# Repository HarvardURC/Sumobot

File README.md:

# Sumobot
Repository for Sumobot

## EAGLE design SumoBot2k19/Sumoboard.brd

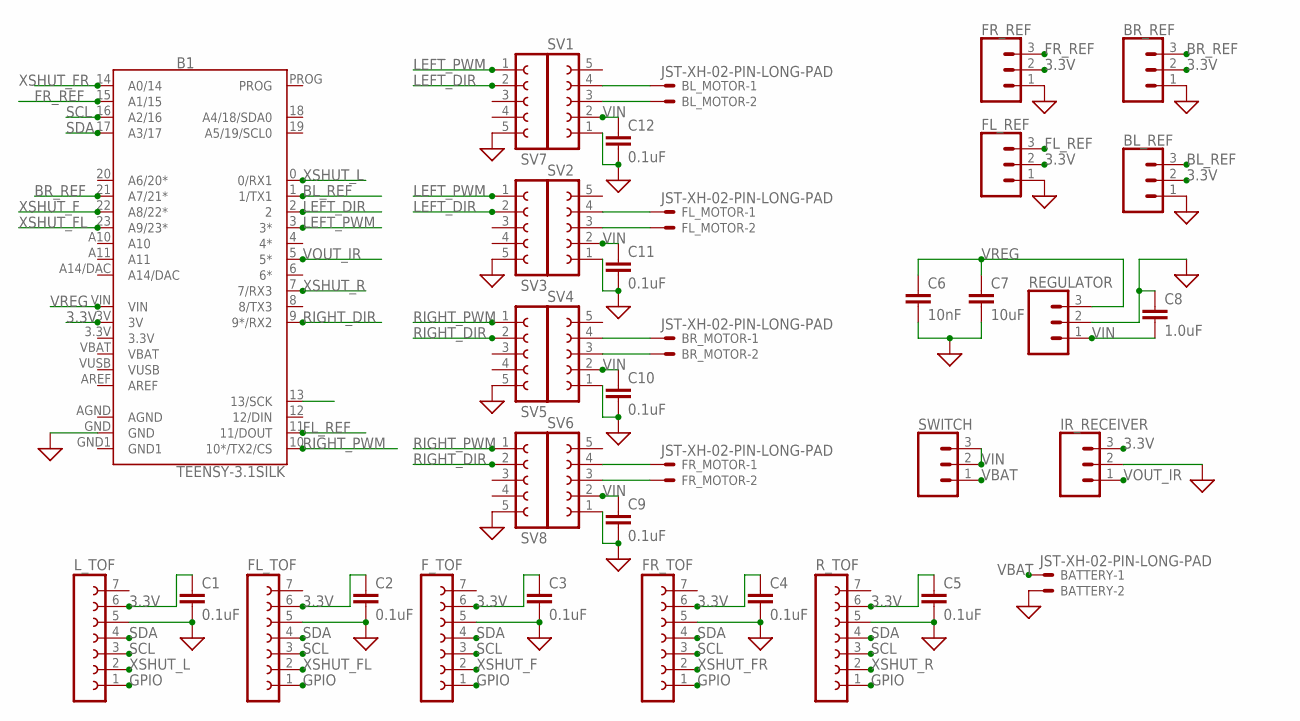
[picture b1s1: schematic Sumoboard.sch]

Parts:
B1: TEENSY-3.1SILK; TEENSY-3.1
BATTERY: JST-XH-02-PIN-LONG-PAD; JST-XH-02-PACKAGE-LONG-PAD
BL_MOTOR: JST-XH-02-PIN-LONG-PAD; JST-XH-02-PACKAGE-LONG-PAD
BL_REF: CONN_03; 1X03
BR_MOTOR: JST-XH-02-PIN-LONG-PAD; JST-XH-02-PACKAGE-LONG-PAD
BR_REF: CONN_03; 1X03
C1, C2, C3, C4, C5, C9, C10, C11, C12: 0.1uF; 0603
C6: 10nF; 0603
C7: 10uF; 0603
C8: 1.0uF; 0603
FL_MOTOR: JST-XH-02-PIN-LONG-PAD; JST-XH-02-PACKAGE-LONG-PAD
FL_REF: CONN_03; 1X03
FL_TOF: FE07-1; FE07
FR_MOTOR: JST-XH-02-PIN-LONG-PAD; JST-XH-02-PACKAGE-LONG-PAD
FR_REF: CONN_03; 1X03
FR_TOF: FE07-1; FE07
F_TOF: FE07-1; FE07
IR_RECEIVER: CONN_03; 1X03
L_TOF: FE07-1; FE07
REGULATOR: CONN_03; 1X03
R_TOF: FE07-1; FE07
SV1, SV2, SV3, SV4, SV5, SV6, SV7, SV8: FE05-1
SWITCH: CONN_03; 1X03

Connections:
3.3V: B1.3.3V, B1.3V, BL_REF.2, BR_REF.2, C1.1, C2.1, C3.1, C4.1, C5.1, FL_REF.2, FL_TOF.6, FR_REF.2, FR_TOF.6, F_TOF.6, IR_RECEIVER.3, L_TOF.6, R_TOF.6
AGND: B1.AGND
BL_REF: B1.1 (1/TX1), BL_REF.3
BR_REF: B1.21 (A7/21*), BR_REF.3
FL_REF: B1.11 (11/DOUT), FL_REF.3
FR_REF: B1.15 (A1/15), FR_REF.3
GND: B1.GND, BATTERY.2, BL_REF.1, BR_REF.1, C1.2, C2.2, C3.2, C4.2, C5.2, C6.2, C7.2, C8.1, C9.2, C10.2, C11.2, C12.2, FL_REF.1, FL_TOF.5, FR_REF.1, FR_TOF.5, F_TOF.5, IR_RECEIVER.2, L_TOF.5, REGULATOR.2, R_TOF.5, SV1.1, SV2.1, SV3.5, SV4.1, SV5.5, SV6.1, SV7.5, SV8.5
GND1: B1.GND1
GPIO: FL_TOF.1, FR_TOF.1, F_TOF.1, L_TOF.1, R_TOF.1
LEFT_DIR: B1.2, SV3.2, SV7.2
LEFT_PWM: B1.3 (3*), SV3.1, SV7.1
unnamed: BL_MOTOR.2, SV1.3
unnamed: BL_MOTOR.1, SV1.4
unnamed: BR_MOTOR.1, SV4.4
unnamed: BR_MOTOR.2, SV4.3
unnamed: FL_MOTOR.1, SV2.4
unnamed: FL_MOTOR.2, SV2.3
unnamed: FR_MOTOR.1, SV6.4
unnamed: FR_MOTOR.2, SV6.3
RIGHT: B1.13 (13/SCK)
RIGHT_DIR: B1.9 (9*/RX2), SV5.2, SV8.2
RIGHT_PWM: B1.10 (10*/TX2/CS), SV5.1, SV8.1
SCL: B1.16 (A2/16), FL_TOF.3, FR_TOF.3, F_TOF.3, L_TOF.3, R_TOF.3
SDA: B1.17 (A3/17), FL_TOF.4, FR_TOF.4, F_TOF.4, L_TOF.4, R_TOF.4
VBAT: B1.VBAT, BATTERY.1, SWITCH.1
VIN: C8.2, C9.1, C10.1, C11.1, C12.1, REGULATOR.1, SV1.2, SV2.2, SV4.2, SV6.2, SWITCH.2, SWITCH.3
VOUT_IR: B1.5 (5*), IR_RECEIVER.1
VREG: B1.VIN, C6.1, C7.1, REGULATOR.3
VUSB: B1.VUSB
XSHUT_F: B1.22 (A8/22*), F_TOF.2
XSHUT_FL: B1.23 (A9/23*), FL_TOF.2
XSHUT_FR: B1.14 (A0/14), FR_TOF.2
XSHUT_L: B1.0 (0/RX1), L_TOF.2
XSHUT_R: B1.7 (7/RX3), R_TOF.2

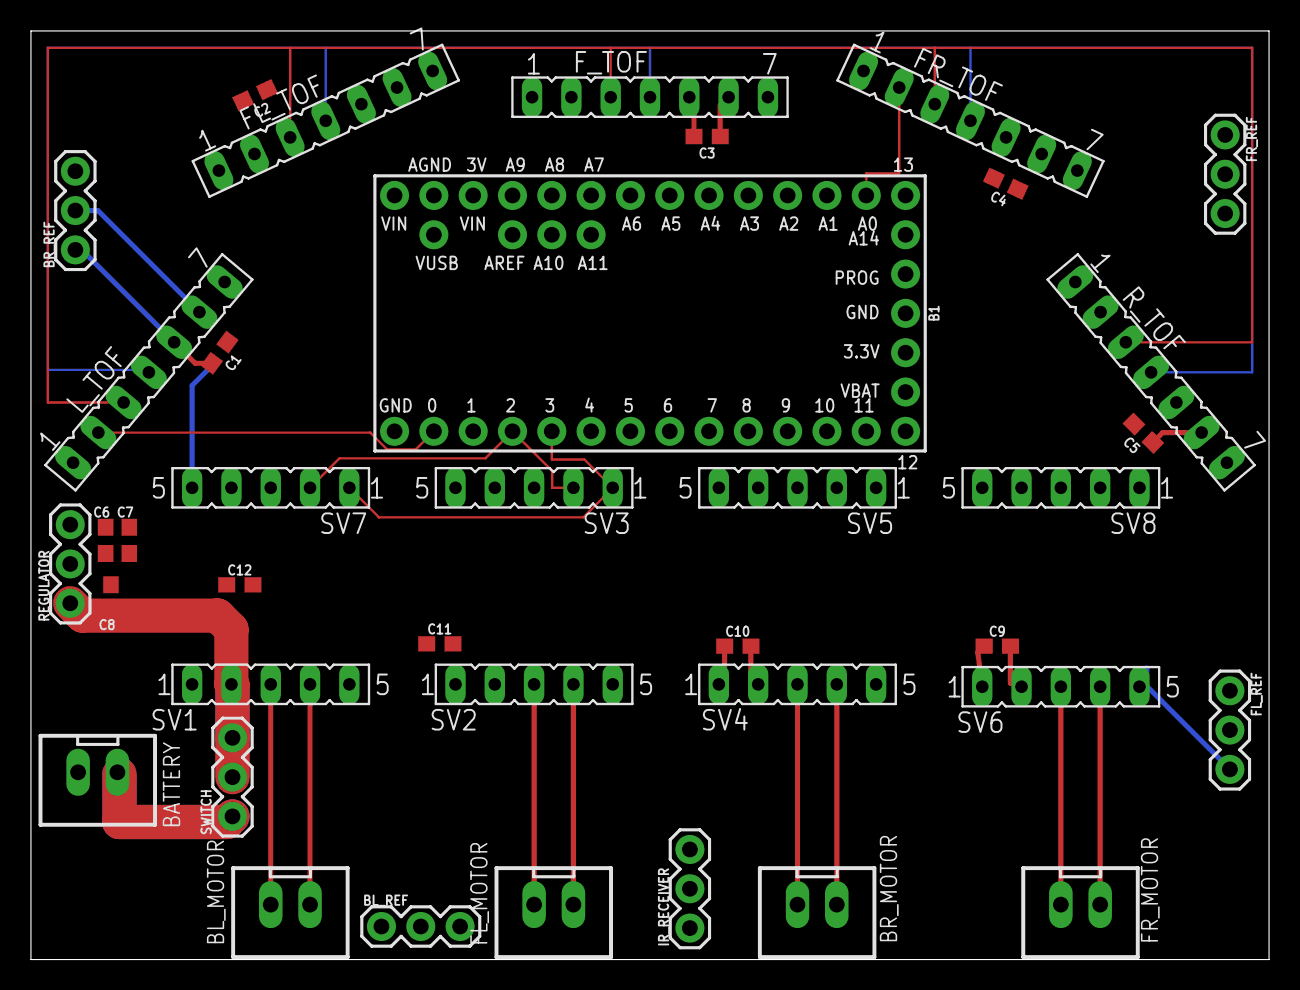
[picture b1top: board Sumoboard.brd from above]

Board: 2 copper layers, 80.0 x 60.0 mm, 38 parts (0 on the bottom side), 30 nets.

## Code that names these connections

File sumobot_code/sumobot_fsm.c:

// CONSTANT declarations
#include <QTRSensors.h>
#include <Wire.h>
#include <VL53L0X.h>

VL53L0X sensor;
QTRSensors qtr;

// `debug` can be set TRUE to output debugging information to the serial port.
const boolean debug = true;   // If TRUE debugging information sent via serial.

// Define time delay constants - they can be adjusted to get the best display.

const int FSM_FREQ = 15;   // Frequency (in Hz) of the FSM
const int ROLL_DELAY = 4;  // Roll time (in Sec) after button released
const int DISP_DELAY = 3;  // Time to display final value (in Sec) before clear.

const int ref_threshhold = 20; // These are dummy threshold values, change these later
const int tof_threshhold = 20; 

const uint8_t SensorCount = 4;
uint16_t sensorValues[SensorCount];
// I/O Pin Constants
#define FL_MOTOR_PIN 3  
#define BL_MOTOR_PIN 4 
#define FR_MOTOR_PIN 9    
#define BR_MOTOR_PIN 10   

#define LEFT_DIR_PIN 2
#define RIGHT_DIR_PIN 8

// L, FL, F, FR, R
#define XSHUT_L 5 
#define XSHUT_FL 6 
#define XSHUT_F 7
#define XSHUT_FR 11
#define XSHUT_R 1
// SCL = 16
// SDA = 17
#define SCL_REF_PIN 16
#define SDA_REF_PIN 17

#define FL_REF 14
#define BL_REF 15
#define FR_REF 20
#define BR_REF 21

#define BUTTON_PIN 12
// Program Variables
int cur_state;      // FSM state variable
                    // 1: Start (init sensors)
                    // 2: Stop (motors = 0)
                    // 3: straight (motors = high)
                    // 4: turn_left (right motors = high)
                    // 5: turn_right (left motors = high)
                    // 6: backup (motors = backwards)
               
/*********************************************************
 * void setup()
 *
 * Runs once. Used to initialize variables
 * and set up I/O pins.
 *********************************************************/
void setup()
{
    // Initialize our I/O pins.
    pinMode(BUTTON_PIN, INPUT_PULLUP);

    pinMode(FL_MOTOR_PIN, OUTPUT);
    pinMode(BL_MOTOR_PIN, OUTPUT);
    pinMode(FR_MOTOR_PIN, OUTPUT);
    pinMode(BR_MOTOR_PIN, OUTPUT);

    pinMode(LEFT_DIR_PIN, OUTPUT);
    pinMode(RIGHT_DIR_PIN, OUTPUT);

    pinMode(SCL_REF_PIN, OUTPUT);
    // pinMode(SDA_REF_PIN, INPUT);

    pinMode(FL_REF, INPUT);
    pinMode(BL_REF, INPUT);
    pinMode(FR_REF, INPUT);
    pinMode(BR_REF, INPUT);

    // configure the sensors
    qtr.setTypeAnalog();
    qtr.setSensorPins((const uint8_t[]){FL_REF, BL_REF, FR_REF, BR_REF}, SensorCount);
    qtr.setEmitterPin(2);

    // need to run qtr.calibrate somewhere

    // Initialize program variables.
    cur_state = 1; // Initialize for 1st state in program loop; wait for input.

   /* Set up serial port if debugging enabled */
    if (debug)
    {
        Serial.begin(9600); // Pipes serial print data to the serial monitor
        Serial.println("Initialization complete.");
    }
}

/*********************************************************
 * boolean checkStart()
 * 
 * Function to see if TEST pushbutton is active
 * 
 * It might seem silly to have this simple test in a function, 
 * but isolating it in a function will make it easy to switch
 * in the more complicated accelerometer later without changing
 * the FSM. In addition it makes replacing polled operation
 * with interrupt operation easier as well.
 * 
 * Returns TRUE if pushbutton pressed; FALSE otherwise
 *********************************************************/

boolean checkStart()
{
    // BUTTON_PIN has a pullup resistor attached, it is LOW when pressed.
    if (digitalRead(BUTTON_PIN) == LOW)
    {
        return true;
    }
    else
    {
        return false;
    }
}

/*********************************************************
 * void loop()
 *  
 * State Machine Loop
 * 
 * Uses the switch/case statement to only execute the code for current state;
 * figures out what the next state is and continues the main program loop. 
 *
 * Runs forever
 *********************************************************/

void loop()
{
    if (debug)               // if debug enabled, print state to serial monitor
    {
        Serial.print("State: ");
        Serial.println(cur_state);
    }

    switch (cur_state)
    {
        // Sensor init
        case 1:                            
            // TODO: init sensors heres (use micromouse init)
            
            // digitalWrite(XSHUT_L, HIGH);
            // digitalWrite(XSHUT_FL, HIGH);
            // digitalWrite(XSHUT_F, HIGH);
            // digitalWrite(XSHUT_FR, HIGH);
            // digitalWrite(XSHUT_R, HIGH);
            cur_state = 2; 
            break;
        // Move init
        case 2:
            // TODO: Set the motors to zero
            if (digitalRead(BUTTON_PIN) == LOW)        // Choose our next state.
            {
                cur_state = 3;
            }
            else
            {
                cur_state = 2;
            }
            break;
        // Straight
        case 3:  
            // TODO: Run the motors straight
            if (!)
            {
                cur_state = 2;
            }
            else if (roll_timeout >= ROLL_DELAY*FSM_FREQ) // Monostable is done.
            {
                roll_timeout = 0;
                cur_state = 4;
            }
            else // Monostable continues, but roll_timeout has been incremented.
            {
                cur_state = 3;
            }
            break;  

        case 4:                                             // Show final value.
            display_timeout++;   // Increment display_timeout b/c on this cycle.
            if (checkStart())    // User re-pressed button; return to rolling.
            {
                cur_state = 2;
            }
            else if (display_timeout >= DISP_DELAY*FSM_FREQ) // Final disp=done.
            {
                // Reset timeout, go to state 1 noting that we need to sleep.
                display_timeout = 0;
                need_sleep = 1;
                cur_state = 1;
            }
            else              // Still have cycles to go before display timeout.
            {
                cur_state = 4;
            } 
            break;
    }
    delay(1000/FSM_FREQ);             // wait for next state machine clock cycle
}

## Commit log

2019-07-15 Made .sch file
2019-07-18 Substituted Winston's file
2019-07-18 Substituted the other WInston file
2019-07-20 added visual GND to schematic
2019-07-20 renamed and changed some pin numbers
2019-07-20 changed motor pins and added motor direction pins
2019-07-20 added bypass capacitors, added IR receiver
2019-07-20 added bypass caps to TOF sensors, motor drivers, and regulator
2019-07-22 connected IR_receiver VOUT pin and TOF sensors' XSHUT pins (see spreadsheet)
2019-07-24 "Changed battery location"
2019-07-24 changed battery location
2019-07-24 Revert "connected IR_receiver VOUT pin and TOF sensors' XSHUT pins (see spreadsheet)"
    This reverts commit f10550aeea0dc74b4494af4baa6c277cfe62f025.
2019-07-24 Reverting back to the previous state of the project at f10550aeea0dc74b4494af4baa6c277cfe62f025
2019-07-24 testing
2019-07-24 Revert "testing"
    This reverts commit c1fed737ae54a1ecceef2a5fc534a1344084b905.
2019-07-25 beginning work on PCB design (unsure whether pinout is up to date)
2019-07-25 moved the reflectance sensors around, removed the unrouted layer to make things more readable
2019-07-26 changed the REF sensor footprints, changed the TOF input voltage (Vin to 3.3V), connected the FL/BL and FR/BR motor PWMs together
2019-07-26 changed the battery footprint
2019-07-28 [code] Adds Motor Abstractions and Motor Pins
    Adds motor abstractions in `motors.cpp` and `motors.hpp`. Also adds the
    pins namespace for later use and populates it with the currently planned
    motor pins.
2019-07-28 Adds .gitignore file
2019-07-30 changed motors and battery to match desired JST-XH footprint on PCB
2019-07-30 added connnections lol
2019-07-30 [code] Adds ToF Sensor Abstractions and Pins
    Adds ToF sensor abstractions in `tof_sensors.cpp` and `tof_sensors.hpp`. Also
    adds ToF sensor pins to the pins namespace. Does not yet include virtual
    ToF class.
2019-07-30 [code] Adds VL53L0X Library with Modification
    In order to work with Teensy, **none** of our code or the code we
    include (libraries) can #include <Wire.h>. It should instead include
    <i2c_t3.h>. The library added here is the pololu VL53L0X using
    <i2c_t3.h> instead of <Wire.h>.
2019-07-30 placed components (all except capacitors) on PCB
2019-07-30 moved components
2019-07-31 placed capacitors
2019-08-01 added connection needs checking
2019-08-01 [code] Adds FSM Draft
2019-08-01 tweeks here and there
2019-08-02 began routing on PCB, moved components around for extra clarity, learned how to align things
2019-08-02 trying to change the left/right pwm/direction pins
2019-08-04 modified TOF, motor driver airway connetions; moved some components around
2019-08-05 added routes
2019-08-05 More connections
2019-08-05 tried adding some routing
2019-08-05 added more routes
2019-08-05 connections yeah!
2019-08-05 changed connections
2019-08-05 more changes :D
2019-08-05 more routes! :D
2019-08-05 more routes!!! :D
2019-08-06 ripped
2019-08-07 [code] Updates Method of Reading from ToF Sensors
    Instead of making us maintain a variable in our main .ino file, have the
    sensor readings for the ToF sensor tracked in a public instance variable
    in the `TofArray` class. This also lets us define the
    `TofArray::objectVisible` function.
2019-08-07 [code] Makes the Linker Happy with the Vector Library
    This is a common issue. See https://forum.pjrc.com/threads/23467-Using-std-vector?p=69787&viewfull=1#post69787
2019-08-07 [code] Adds First Full Version of the FSM
2019-08-07 rerouting
2019-08-07 fewer snakes :D
2019-08-07 added more routes; see motor drivers and regulator (wasn't sure of thickness)
2019-08-07 [code] Changes Sumobot Drive Value to be #defined
2019-08-07 merged and resolved conflict (I hope) on board
2019-08-07 checking to see if file is still alive
2019-08-07 connected sensors :DD
2019-08-08 rerouted motor drivers
2019-08-08 need to check battery connection
2019-08-08 deleted GPIO pins
2019-08-08 added rats nest
2019-08-08 routed GND and VIN
2019-08-08 airwire routes
2019-08-09 [code] Converts fsm State Variable to Enum

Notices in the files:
parts and their libraries:
SparkFun-Boards: Licensing: Creative Commons ShareAlike 4.0 International - https://creativecommons.org/licenses/by-sa/4.0
